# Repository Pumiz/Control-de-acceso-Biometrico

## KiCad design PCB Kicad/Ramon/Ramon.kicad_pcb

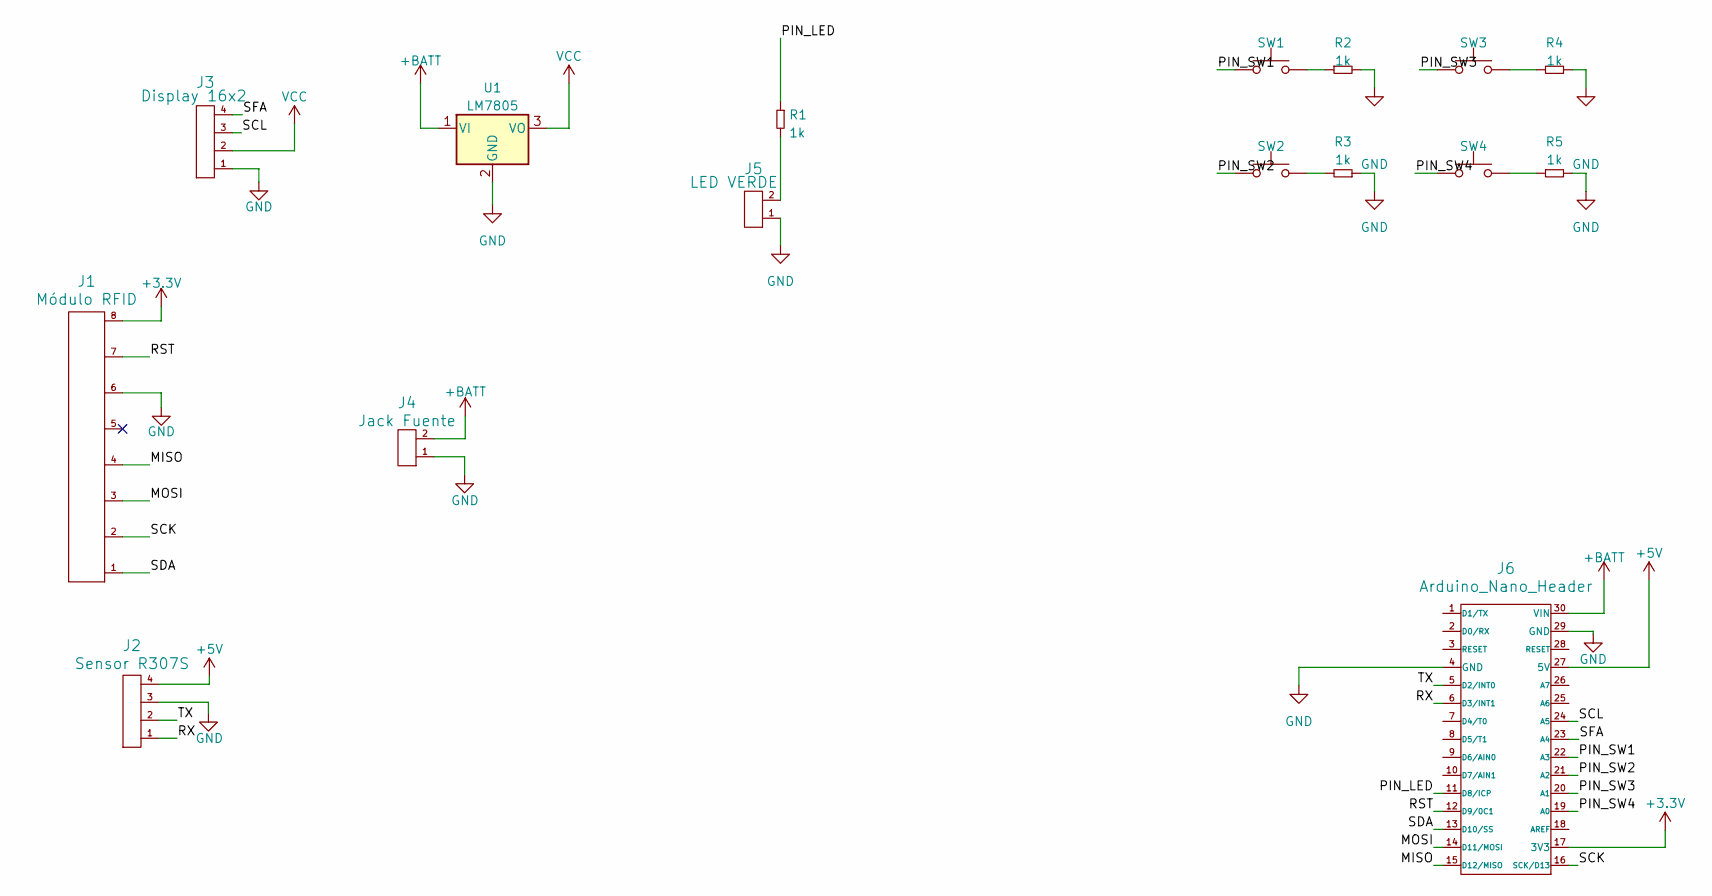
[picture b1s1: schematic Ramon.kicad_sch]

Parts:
J1: Módulo RFID; Pin_Header_Straight_1x08
J2: Sensor R307S; pin_strip_4
J3: Display 16x2; pin_strip_4
J4: Jack Fuente; BORNERA2_AZUL
J5: LED VERDE; BORNERA2_AZUL
J6: Arduino_Nano_Header; arduino_nano_header
R1, R2, R3, R4, R5: 1k; RES0.3
SW1, SW2, SW3, SW4: SW_Push; BORNERA2_AZUL
U1: LM7805; TO-220-3_Vertical

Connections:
+3.3V: J1.8, J6.17 (3V3)
+5V: J2.4, J6.27 (5V)
+BATT: J4.2, J6.30 (VIN), U1.1 (VI)
/MISO: J1.4, J6.15 (D12/MISO)
/MOSI: J1.3, J6.14 (D11/MOSI)
/PIN_LED: J6.11 (D8/ICP), R1.1
/PIN_SW1: J6.22 (A3), SW1.1
/PIN_SW2: J6.21 (A2), SW2.1
/PIN_SW3: J6.20 (A1), SW3.1
/PIN_SW4: J6.19 (A0), SW4.1
/RST: J1.7, J6.12 (D9/0C1)
/RX: J2.1, J6.6 (D3/INT1)
/SCK: J1.2, J6.16 (SCK/D13)
/SCL: J3.3, J6.24 (A5)
/SDA: J1.1, J6.13 (D10/SS)
/SFA: J3.4, J6.23 (A4)
/TX: J2.2, J6.5 (D2/INT0)
GND: J1.6, J2.3, J3.1, J4.1, J5.1, J6.4 (GND), J6.29 (GND), R2.2, R3.1, R4.1, R5.2, U1.2 (GND)
unnamed: J5.2, R1.2
unnamed: R2.1, SW1.2
unnamed: R3.2, SW2.2
unnamed: R4.2, SW3.2
unnamed: R5.1, SW4.2
VCC: J3.2, U1.3 (VO)

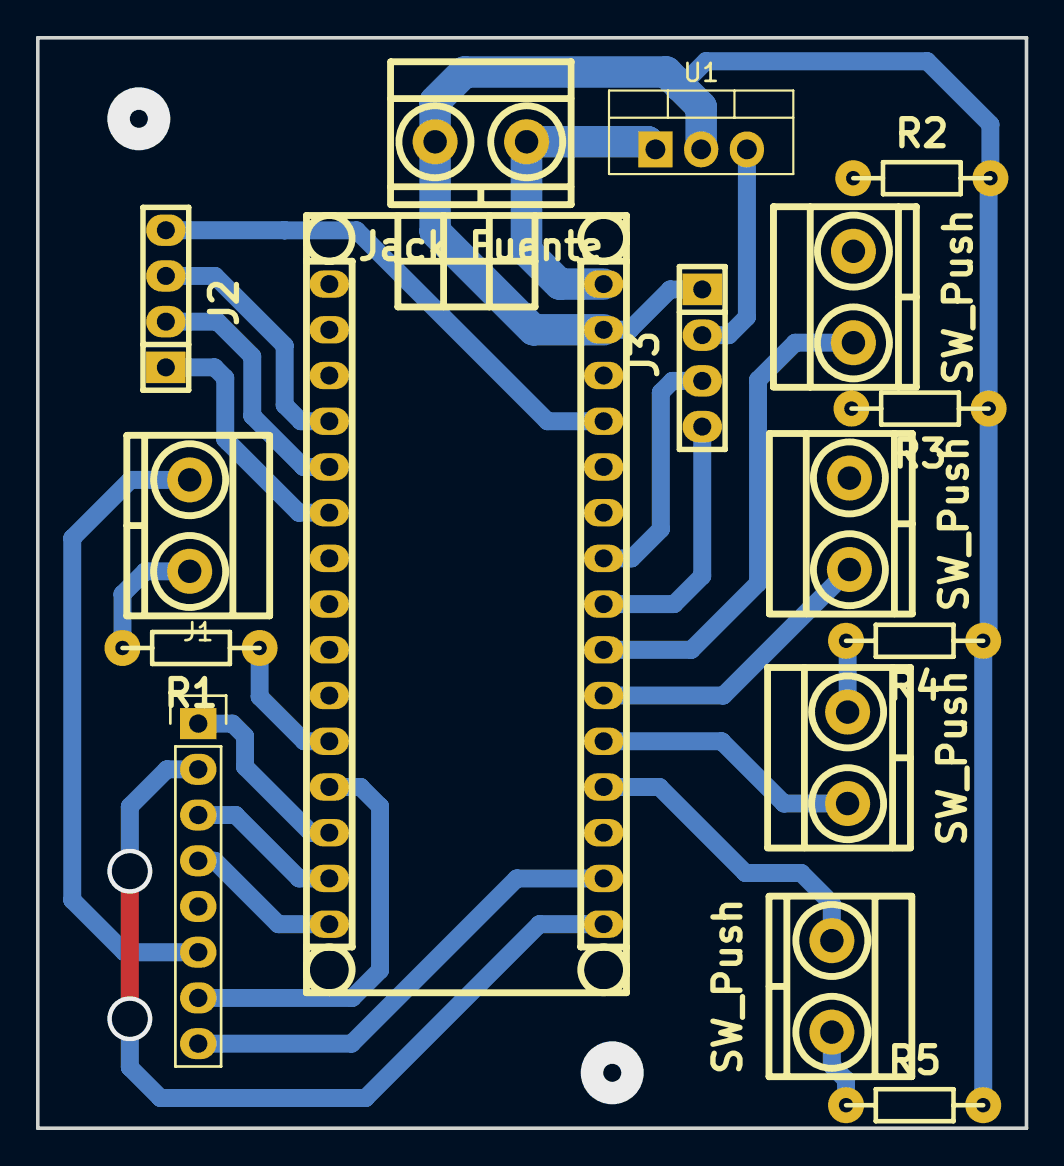
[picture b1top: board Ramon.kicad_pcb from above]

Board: 2 copper layers, 54.9 x 60.6 mm, 16 parts (0 on the bottom side), 24 nets.

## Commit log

2023-06-05 Se agregó la librería del sensor
2023-06-05 Se agregó la libreria del sensor
2023-06-06 Carpeta de codigos para guardar, eliminar y comprar huellas.
2023-06-08 Se agregó la librería para el modulo I2C del display
2023-06-08 Se creo la carpeta para los diseños 3D
2023-06-09 Se Agrego el ejemplo del pulsador PullUp y del Display
2023-06-16 Se agregó la placa del proyecto
2023-06-16 Agregue la libreria del modulo RFID
2023-06-16 Codigo de pruebas del RFID
2023-06-16 Codigo del printeo con el display e I2C
